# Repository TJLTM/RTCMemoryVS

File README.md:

# RTCMemoryVS
basically an addon board for some other projects to have an external battery for the RTC or anything else that needs to have a voltage to maintain memory. 

Vin max - 14

Battery max voltage - 3.6 

Output Votlage - 3.3 

Max Current - 500mA but should only do about 100-250mA  

using a MAX6326 and a switching voltage regulator to supply 3.3 voltage to maintain a RTC or other electrical devices with a battery or from an always on votlage source.

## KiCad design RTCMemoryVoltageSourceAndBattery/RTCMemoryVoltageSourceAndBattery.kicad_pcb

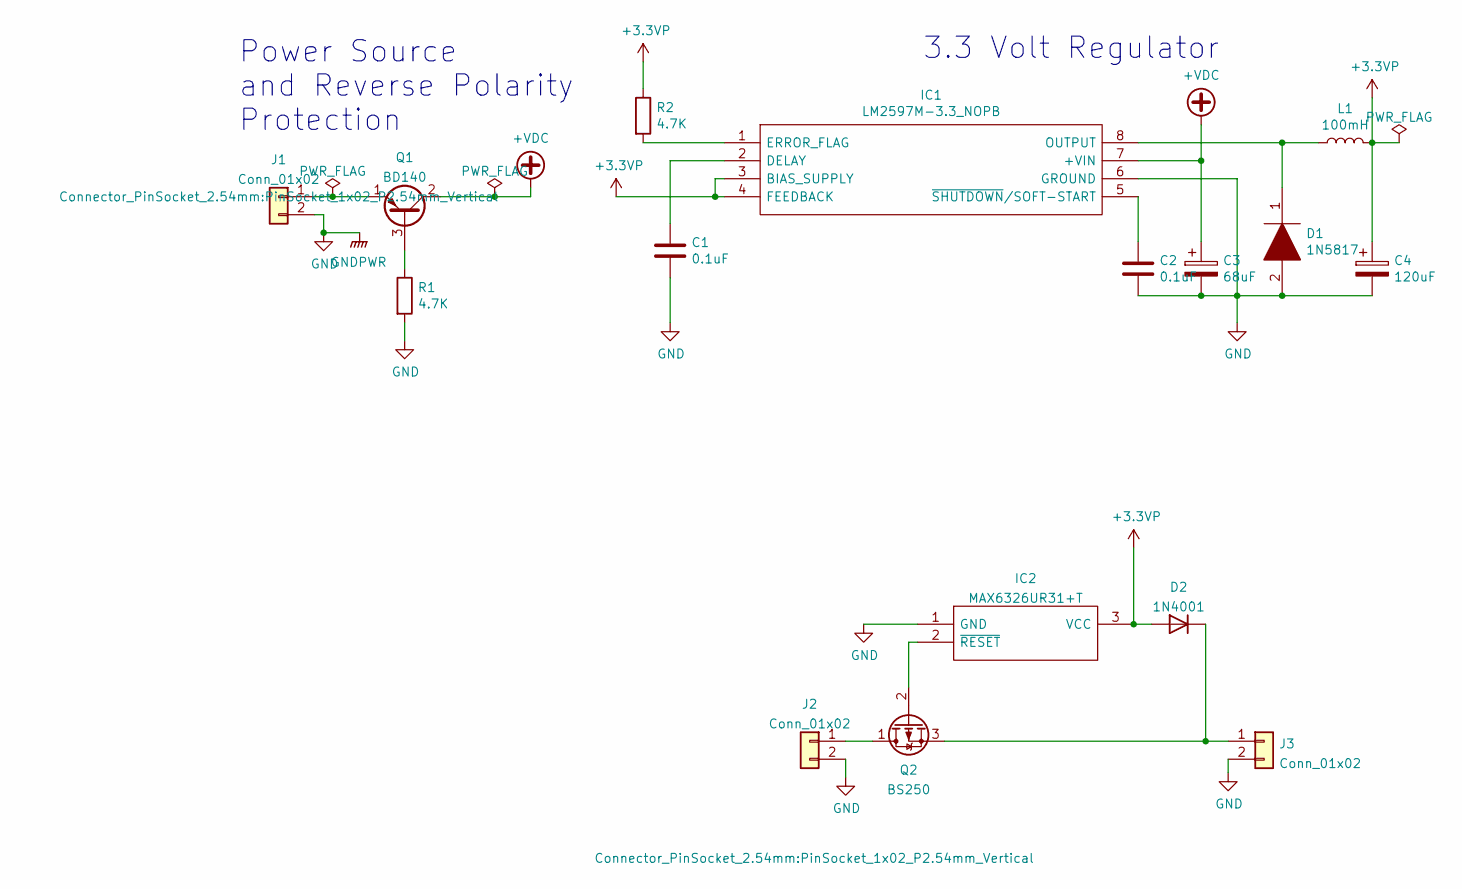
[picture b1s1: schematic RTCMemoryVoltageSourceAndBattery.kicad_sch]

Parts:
C1, C2: 0.1uF; C_Rect_L9.0mm_W3.6mm_P7.50mm_MKT
C3: 68uF; CP_Radial_D5.0mm_P2.50mm
C4: 120uF; CP_Radial_D8.0mm_P5.00mm
D1: 1N5817; DIOAD1414W86L464D238; Mouser Part Number 511-1N5817
D2: 1N4001; D_DO-41_SOD81_P10.16mm_Horizontal
IC1: LM2597M-3.3_NOPB; SOIC127P600X175-8N; Mouser Part Number 926-LM2597M-33/NOPB
IC2: MAX6326UR31+T; SOT95P237X112-3N; Mouser Part Number 700-MAX6326UR31T
J1, J2, J3: Conn_01x02; PinSocket_1x02_P2.54mm_Vertical
L1: 100mH; L_Axial_L9.5mm_D4.0mm_P15.24mm_Horizontal_Fastron_SMCC
Q1: BD140; TO-126-3_Vertical
Q2: BS250; TO-92_Inline
R1, R2: 4.7K; R_Axial_DIN0207_L6.3mm_D2.5mm_P2.54mm_Vertical

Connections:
+3.3VP: C4.1, D2.2 (A), IC1.3 (BIAS_SUPPLY), IC1.4 (FEEDBACK), IC2.3 (VCC), L1.2, R2.1
+VDC: C3.1, IC1.7 (+VIN), Q1.2 (C)
GND: C1.2, C2.2, C3.2, C4.2, D1.2, IC1.6 (GROUND), IC2.1 (GND), J1.2, J2.2, J3.2, R1.2
unnamed: C1.1, IC1.2 (DELAY)
unnamed: C2.1, IC1.5 (~SHUTDOWN/SOFT-START)
unnamed: D1.1, IC1.8 (OUTPUT), L1.1
unnamed: D2.1 (K), J3.1, Q2.3 (S)
unnamed: IC1.1 (ERROR_FLAG), R2.2
unnamed: IC2.2 (~RESET), Q2.2 (G)
unnamed: J2.1, Q2.1 (D)
unnamed: J1.1, Q1.1 (E)
unnamed: Q1.3 (B), R1.1

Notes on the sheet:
Power Source and Reverse Polarity Protection
3.3 Volt Regulator

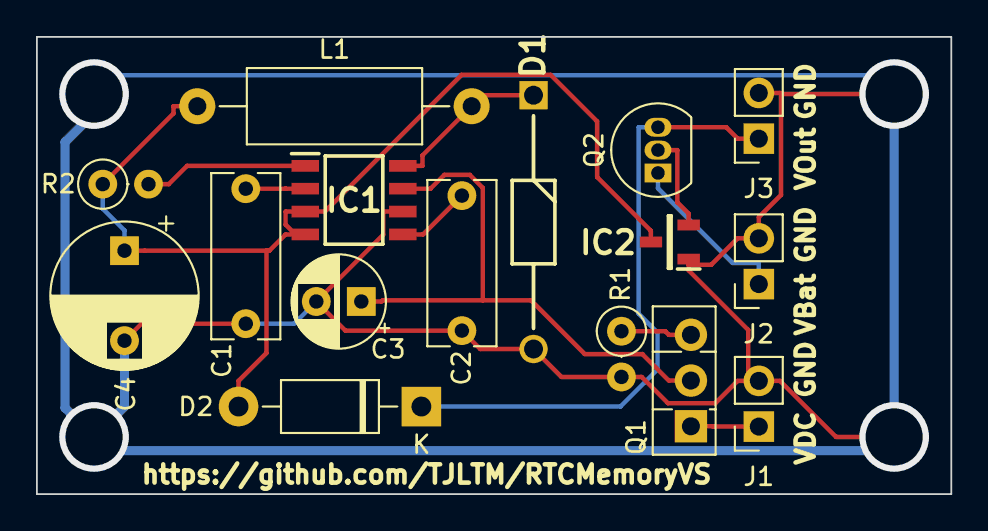
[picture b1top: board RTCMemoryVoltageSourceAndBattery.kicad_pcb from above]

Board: 2 copper layers, 50.8 x 25.4 mm, 16 parts (0 on the bottom side), 12 nets.

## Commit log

2022-02-09 initial Kicad
2022-02-17 continuing schem wip
2022-02-19 Routed and labeled. Ready for Fab
2022-02-19 fab files
2022-02-19 didnt' save the pcb file
2022-02-20 fixing these for resubmit.
2022-03-23 adding BOM
